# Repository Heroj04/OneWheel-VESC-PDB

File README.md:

# OneWheel-VESC-PDB
A simple PDB PCB for DIY VESC OneWheel builds. Using split battery packs and an Ennoid X-Lite BMS.

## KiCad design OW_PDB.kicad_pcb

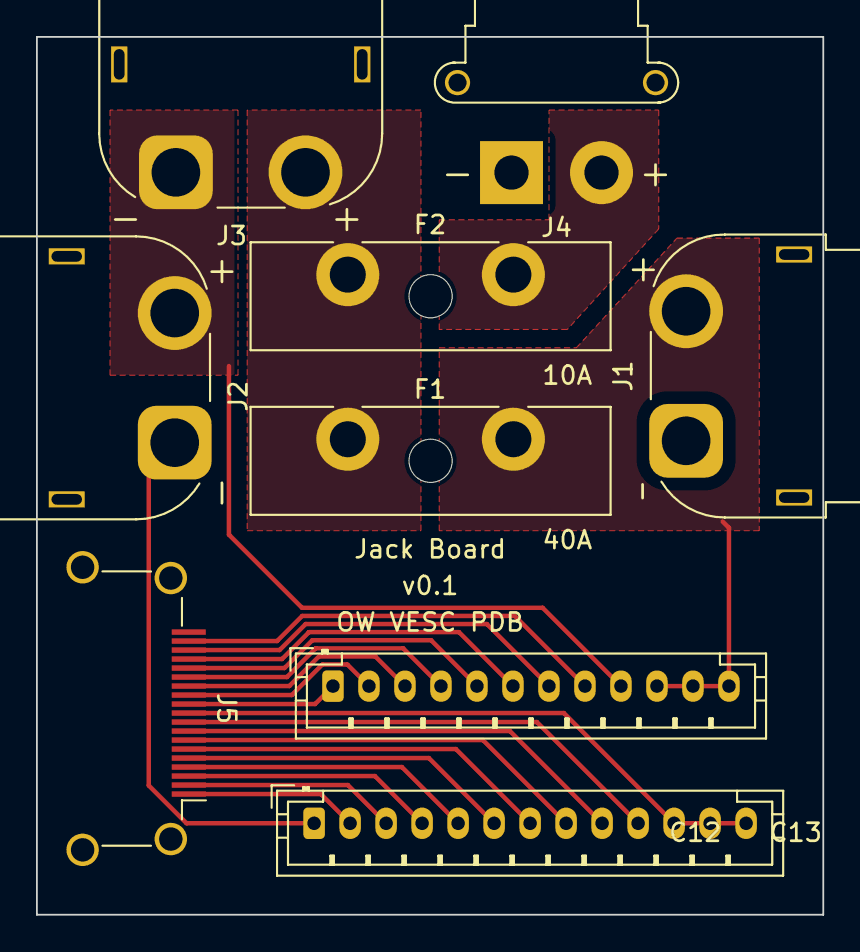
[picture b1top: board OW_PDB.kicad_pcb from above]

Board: 2 copper layers, 43.7 x 48.8 mm, 9 parts (0 on the bottom side), 23 nets.

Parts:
F1: 40A Fuse; Fuseholder_Blade_ATO_Littelfuse_Pudenz_2_Pin
F2: 10A Fuse; Fuseholder_Blade_ATO_Littelfuse_Pudenz_2_Pin
J1: XT60 VESC; AMASS_XT60PW-F_1x02_P7.20mm_Horizontal
J2: XT60 Main Battery; AMASS_XT60PW-M_1x02_P7.20mm_Horizontal
J3: XT60 Expansion Cell; AMASS_XT60PW-M_1x02_P7.20mm_Horizontal
J4: XT30 XLite Battery; AMASS_XT30PW-F_1x02_P2.50mm_Horizontal
J5: HDMI Balance; HDMI_A_Amphenol_10029449-x01xLF_Horizontal
J6: JST-PH XLite Balance C13-24; JST_PH_B12B-PH-K_1x12_P2.00mm_Vertical
J7: JST-PH XLite Balance C0-12; JST_PH_B13B-PH-K_1x13_P2.00mm_Vertical

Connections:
unnamed: J2.2, J3.1, J6.9
unnamed: J1.1, J2.1, J4.1, J7.1
unnamed: F1.1, F2.1, J3.2
unnamed: F1.2, J1.2, J6.10, J6.11, J6.12
unnamed: F2.2, J4.2
unnamed: J5.1, J7.2
unnamed: J5.2, J7.3
unnamed: J5.3, J7.4
unnamed: J5.4, J7.5
unnamed: J5.5, J7.6
unnamed: J5.6, J7.7
unnamed: J5.7, J7.8
unnamed: J5.8, J7.9
unnamed: J5.9, J7.10
unnamed: J5.10, J7.11, J7.12, J7.13
unnamed: J5.11, J6.1
unnamed: J5.12, J6.2
unnamed: J5.13, J6.3
unnamed: J5.14, J6.4
unnamed: J5.15, J6.5
unnamed: J5.16, J6.6
unnamed: J5.17, J6.7
unnamed: J5.18, J6.8

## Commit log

2023-04-13 Initial Project Upload
2023-04-27 Make connections closer on PCB
